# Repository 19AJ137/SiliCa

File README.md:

# SiliCa

`SiliCa` は、JIS X 6319-4（`FeliCa`）互換の非接触型 IC カードです。  
マイコンとして `ATtiny1616` を採用しており、外部電源を必要とせず、カードリーダからの給電によって動作します。

## 概要

`SiliCa` は、最小限のハードウェア構成で、 `FeliCa` プロトコルをファームウェアによって再現し、`FeliCa Standard` や `FeliCa Lite-S` のエミュレーションを実現することを目的としています。

また、`SiliCa` では、実際の `FeliCa` カードで書き換えが不可能な `IDm` やシステムコードなどのパラメータを自由に書き換えることができます。

詳細な仕様や使用方法については、寄稿した同人誌 [rand_r(&v3)](https://techbookfest.org/product/an6q3RzcSM0RcWQBevrEM9) をご参照ください。

## 回路図

## 注意事項

本プロジェクトは、学術的および実験的な目的で提供されており、商業利用や実際の運用を目的としたものではありません。

---

```
FeliCaは、ソニー株式会社が開発した非接触ICカードの技術方式です。
FeliCaは、ソニーグループ株式会社の登録商標です。
本文では™、®は明記していません。
```

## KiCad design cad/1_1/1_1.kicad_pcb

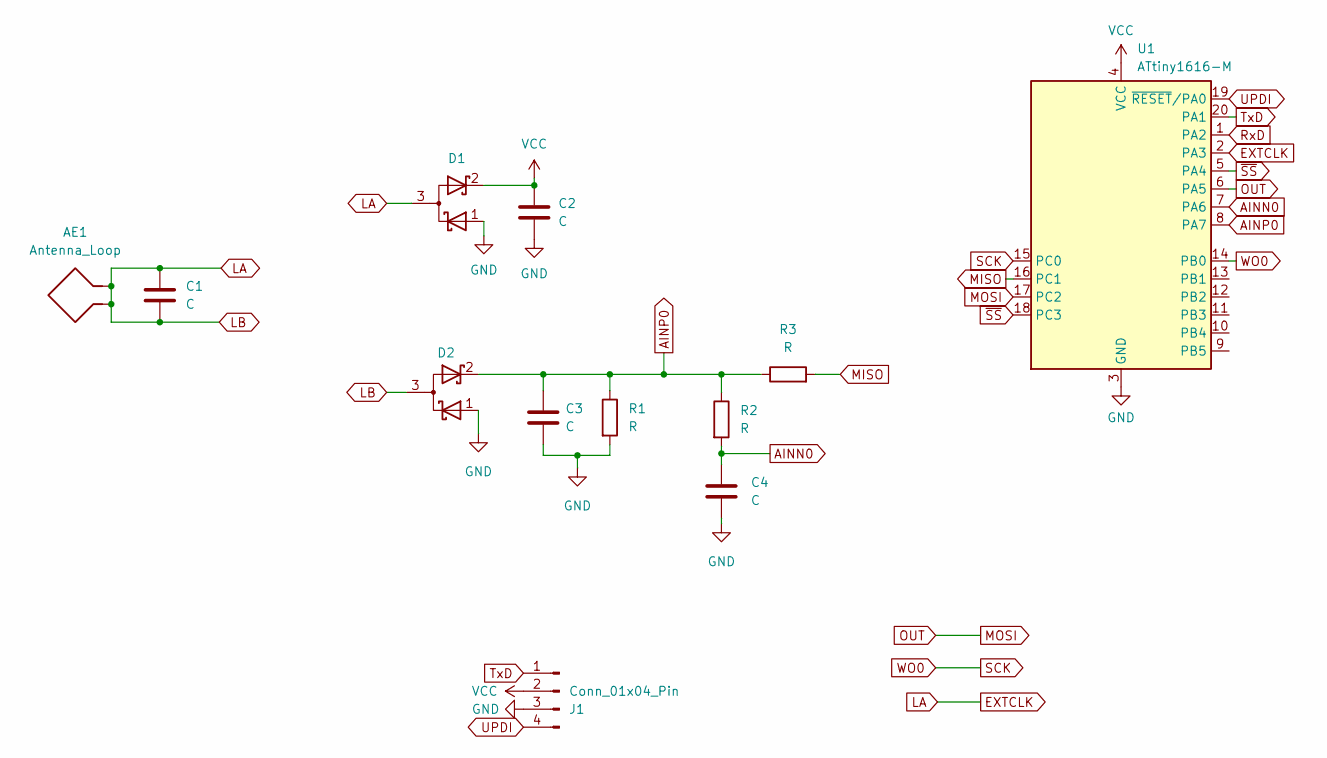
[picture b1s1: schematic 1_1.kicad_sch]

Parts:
AE1: Antenna_Loop; PinHeader_1x02_P2.54mm_Vertical
C1, C2, C3, C4: C; C_0402_1005Metric
D1, D2: D_Schottky_Dual_Series_AKC_Parallel; SOT-523
J1: Conn_01x04_Pin; PinHeader_1x04_P2.54mm_Vertical
R1, R2, R3: R; R_0402_1005Metric
U1: ATtiny1616-M; VQFN-20-1EP_3x3mm_P0.4mm_EP1.7x1.7mm

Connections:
AINN0: C4.1, R2.2, U1.7 (PA6)
AINP0: C3.1, D2.2 (K), R1.1, R2.1, R3.1, U1.8 (PA7)
EXTCLK: AE1.1, AE1.2, C1.1, C1.2, D1.3 (A), D2.3 (A), U1.2 (PA3)
GND: C2.2, C3.2, C4.2, D1.1 (K), D2.1 (K), J1.3, R1.2, U1.3 (GND), U1.21 (GND)
MISO: R3.2, U1.16 (PC1)
MOSI: U1.6 (PA5), U1.17 (PC2)
RxD: U1.1 (PA2)
SCK: U1.14 (PB0), U1.15 (PC0)
TxD: J1.1, U1.20 (PA1)
UPDI: J1.4, U1.19 (~RESET/PA0)
VCC: C2.1, D1.2 (K), J1.2, U1.4 (VCC)
~SS: U1.5 (PA4), U1.18 (PC3)

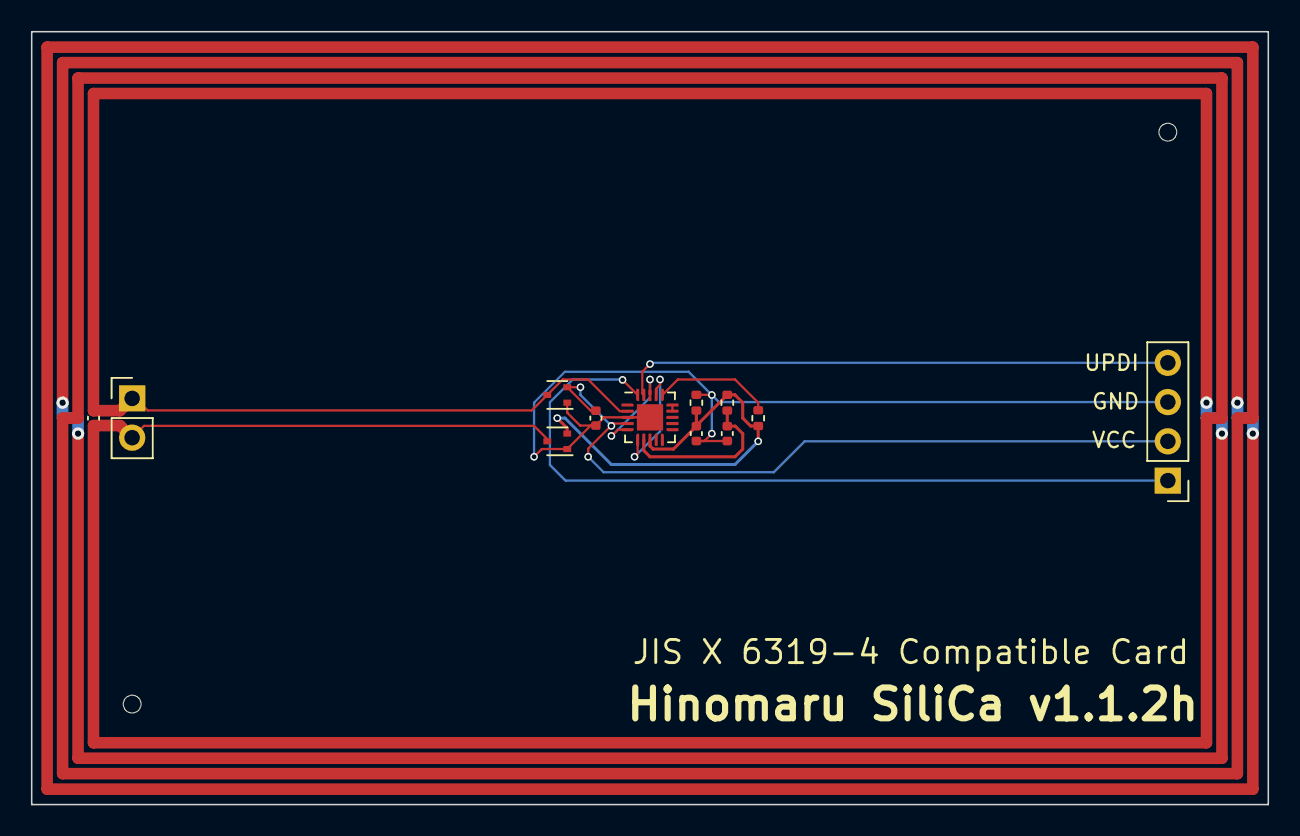
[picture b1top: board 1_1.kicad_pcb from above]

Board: 2 copper layers, 80.0 x 50.0 mm, 12 parts (0 on the bottom side), 11 nets.

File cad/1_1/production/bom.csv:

Designator,Footprint,Quantity,Value,LCSC Part #
AE1,PinHeader_1x02_P2.54mm_Vertical,1,Antenna_Loop,
C1,0402,4,C,C1567
C2,0402,4,C,C15195
C3,0402,4,C,C1523
C4,0402,4,C,C1523
D1,SOT-523,2,D_Schottky_Dual_Series_AKC_Parallel,C2919808
D2,SOT-523,2,D_Schottky_Dual_Series_AKC_Parallel,C2919808
J1,PinHeader_1x04_P2.54mm_Vertical,1,Conn_01x04_Pin,
R1,0402,3,R,C11702
R2,0402,3,R,C11702
R3,0402,3,R,C25123
U1,VQFN-20-1EP_3x3mm_P0.4mm_EP1.7x1.7mm,1,ATtiny1616-M,C507118

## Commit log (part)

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2025-10-17 copy KiCad files
2025-10-17 move files
2025-10-18 add pio sources
2025-10-18 remove unnecessary files
2025-10-18 rename dump_command to print_packet and update parameter usage
2025-10-18 change comment
2025-10-19 add command.py
2025-10-19 fix: update service_code_eep to pointer type and adjust EEPROM read/write calls
2025-10-19 fix: validate command length in process function to prevent errors
2025-10-19 refactor: clarify comments for original and AI generated code performance
2025-10-21 fix: correct service_code_eep pointer usage and adjust variable visibility
2025-10-21 fix: update status flag in response and improve error logging for read/write operations
2025-10-21 refactor: rename rx_buf to raw_buf and streamline data handling functions
2025-10-21 fix: add 'kbps' to cSpell.words for improved spell checking
2025-10-21 improve performance
2025-10-22 fix: update hysteresis setting for Analog Comparator 0 to 50mV
2025-10-22 feat: add .gitignore to exclude backup and cache files
2025-10-23 feat: add ADC configuration and hysteresis adjustment for improved voltage reference handling
2025-10-23 little fix
2025-10-23 fix: adjust hysteresis settings for Analog Comparator based on reference value
2025-10-25 move UPDI wire to back
2025-10-25 fix: update version number to 1.1.2 in PCB layout
2025-10-25 add tooling holes
2025-10-25 move tooling holes
2025-10-25 refactor: remove unused reference text and reset active layer to default
2025-10-25 refactor silica.cpp
2025-10-25 refactor: improve comments and add delay for signal stabilization in send_response
2025-10-25 refactor: remove unused no_connect element from schematic
2025-10-25 refactor: improve transmit handling
2025-10-25 refactor: fix SPI_transfer function signature and update calls in enable_transmit
2025-10-26 add receive_packet
2025-10-26 refactor: simplify receive_packet and improve get_shift_from_sync logic
2025-10-26 refactor: add delay for Polling command in loop function
2025-10-28 refactor: enhance frame capture and synchronization logic in receive_command
2025-10-28 refactor: update system code handling and improve polling command delay
2025-10-28 refactor: implement parse_block_list function and improve block handling in read_without_encryption
2025-10-28 refactor: improve packet length validation and error handling in receive_command
2025-10-29 refactor: enhance comments for clarity in main application and data link layers
2025-10-29 refactor: enhance card sensing by adding iterations and interval parameters
2025-10-29 refactor: modify test_response to continuously send polling response
2025-10-31 docs: update README with detailed project description and add images
2025-10-31 docs: correct terminology in README and add reference to contributed publication
2025-11-02 refactor: remove unnecessary eeprom_busy_wait calls in main application
2025-11-02 feat: add write_silica.py for writing data to SiliCa tags
2025-11-02 refactor: enhance write_silica.py with improved command handling and error checking
2025-11-03 refactor: update parse_block_list to return size and adjust related logic in write_without_encryption
2025-11-03 fix: update U1 rotation in positions.csv from 0.0 to 270.0
2025-11-06 202511061430
2025-11-06 202511062320
2025-11-07 docs: add licensing and contact information to README.md
2025-11-12 feat: implement request_service function and integrate into process command flow
2025-11-13 Refine README.md for clarity and consistency in language
2025-11-14 Update README.md to correct reference to published work
2025-11-23 Add how to order guide for SiliCa using JLCPCB
2025-11-25 Add handling for D_ID, SER_C, and SYS_C blocks in read_without_encryption
2025-11-25 Update write_system_block to update IDm on block write and ensure data integrity
2026-01-09 refactor code
2026-01-09 optimize code
2026-01-10 add deploy.sh (#4)
2026-02-09 全体的に部品を左上に移動した TxDとRxDを接続した
2026-02-09 Add production files
2026-02-09 Update component positions and configuration in PCB design files
2026-05-17 convert to KiCad 10.0
2026-05-17 Add .history/ to .gitignore
